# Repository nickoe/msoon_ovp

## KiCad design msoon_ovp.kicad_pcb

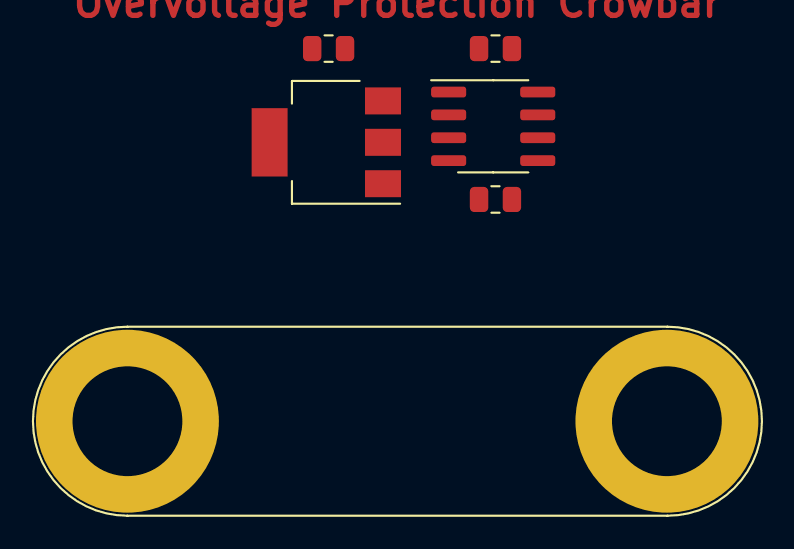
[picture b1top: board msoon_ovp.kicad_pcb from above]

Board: 2 copper layers, 6 parts (0 on the bottom side), 4 nets, no tracks yet.

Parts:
D1: Q_SCR_KAGA; SOT-223
J1: Conn_01x02; Banana_Jack_2Pin
R1, R2, R3: R; R_0805_2012Metric
U1: LM285M-ADJ; SOIC-8_3.9x4.9mm_P1.27mm

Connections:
GND: D1.1, J1.2, R2.2, U1.4
unnamed: D1.3, R3.2, U1.8
unnamed: R1.2, R2.1, U1.5
VCC: D1.2, D1.4, J1.1, R1.1, R3.1

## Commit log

2020-09-27 Add gitignore
2020-09-27 Annotate and add tran directive to schematic
2020-10-30 Add TL431 model
2020-10-30 Something, dunno what
    ... does not matter much, we will discard this and just add zers instead
    of a fancy crowbar.
